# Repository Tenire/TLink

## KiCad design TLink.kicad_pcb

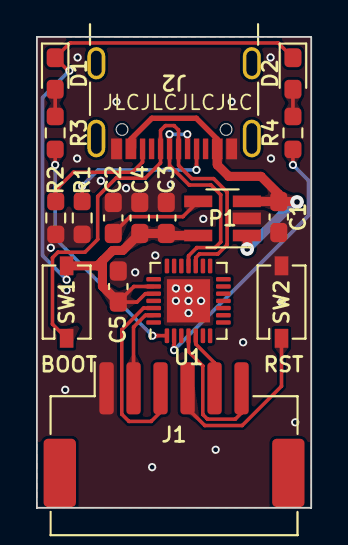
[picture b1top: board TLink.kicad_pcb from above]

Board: 2 copper layers, 15.2 x 26.2 mm, 17 parts (0 on the bottom side), 17 nets.

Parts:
C1, C3, C5: 100nF; C_0603_1608Metric_Pad1.08x0.95mm_HandSolder
C2: 10nF; C_0603_1608Metric_Pad1.08x0.95mm_HandSolder
C4: 10μF; C_0603_1608Metric_Pad1.08x0.95mm_HandSolder
D1, D2: LED_Small; LED_0603_1608Metric_Pad1.05x0.95mm_HandSolder
J1: ZH_01x06; JST_ZE_SM06B-ZESS-TB_1x06-1MP_P1.50mm_Horizontal
J2: TYPEC-304S-ACP16; USB_C_Receptacle_GCT_USB4105-xx-A_16P_TopMnt_Horizontal
P1: RT9013-33GB; SOT-23-5_HandSoldering
R1, R2, R3, R4: 5.1k; R_0603_1608Metric_Pad0.98x0.95mm_HandSolder
SW1, SW2: SW_SPST; Button_Turtle_3x4x2_180
U1: CH549F; QFN-28-1EP_4x4mm_P0.4mm_EP2.4x2.4mm

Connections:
+3V3: C3.1, C4.1, C5.1, D1.1 (K), D2.1 (K), P1.5 (VOUT), SW1.2 (B), U1.23 (VDD), U1.24 (V33)
+5V: C1.1, J2.A4 (VBUS_1), J2.A9 (VBUS_2), J2.B4 (VBUS_3), J2.B9 (VBUS_4), P1.1 (VIN), P1.3 (EN)
/DN: J2.A7 (DN1), J2.B7 (DN2), U1.18 (P5.0/DM/UDM)
/DP: J2.A6 (DP1), J2.B6 (DP2), SW1.1 (A), U1.17 (P5.1/DP/UDP)
/LED_CON: R4.1, U1.2 (P1.7/SCK/TXD1/AIN7)
/LED_RUN: R3.1, U1.1 (P1.6/MISO/RXD1/VBUS/AIN6)
/RST: J1.4, SW2.1 (A)
/RX: J1.6, U1.4 (P3.0/RXD)
/SWCLK: J1.2, U1.27 (P1.4/SCS/UCC1/AIN4)
/SWDIO: J1.3, U1.26 (P1.1/T2EX/CAP2/AIN1)
/TX: J1.5, U1.5 (P3.1/TXD)
GND: C1.2, C2.1, C3.2, C4.2, C5.2, J1.1, J2.A1 (GND_1), J2.A12 (GND_2), J2.B1 (GND_3), J2.B12 (GND_4), P1.2 (GND), R1.2, R2.2, SW2.2 (B), U1.29 (GND)
unnamed: D1.2 (A), R3.2
unnamed: D2.2 (A), R4.2
unnamed: J2.A5 (CC1), R1.1
unnamed: J2.B5 (CC2), R2.1
unnamed: C2.2, P1.4 (NC)

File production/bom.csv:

Designator,Footprint,Quantity,Value,LCSC Part #
"C1, C3, C5",0603,3,100nF,
C2,0603,1,10nF,
C4,0603,1,10μF,
"D1, D2",0603,2,LED_Small,
J1,JST_ZE_SM06B-ZESS-TB_1x06-1MP_P1.50mm_Horizontal,1,ZH_01x06,
J2,USB_C_Receptacle_GCT_USB4105-xx-A_16P_TopMnt_Horizontal,1,TYPEC-304S-ACP16,
P1,SOT-23-5_HandSoldering,1,RT9013-33GB,
"R1, R2, R3, R4",0603,4,5.1k,
"SW1, SW2",Button_Turtle_3x4x2_180,2,SW_SPST,
U1,QFN-28-1EP_4x4mm_P0.4mm_EP2.4x2.4mm,1,CH549F,

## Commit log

2023-05-14 TLink V1.0 For ARM/RiSC-V
2023-05-21 TLink v1.1 For ARM/RISC-V
